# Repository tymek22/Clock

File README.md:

# Clock

<br>This smart Clock is made to resemble a traditional wall clock. It shows the time using two rings of RGB LEDs. The inner (smaller) ring is for the hours, while the outer circumference displays the minutes together with the seconds.
<br>The clock is a smart clock, it features a microcontroller which has BLE connectivity. By using a mobile application, the clock can be controlled wirelessly. Below is a photo of the clock showing the time 9:41

## <b>Components</b><br>
The clock is built from various components and materials. The main ones are:
 - Frame, 3D printed
 - Power supply, 5V adapter with sufficient power
 - RGB LED strips, 1 strip of 60 and 1 strip of 48 LEDs (WS2812b)
 - PIR sensor
 - CR2032 battery
 - Wires
 - PCB
 - Other components for the PCB
 
## <b>Frame</b><br>
 
 The frame has been designed in Autodesk Fusion 360. It looks like this:<br>
 <br>
 
 The electronics are placed inside, the only components which are outside of the clock body are the LEDs as well as the wires to a power adapter. Below on the left, you can see the inside of the body and on the right, how it looks in reality.<br>

<p>&nbsp;</p>
Because of all those wires, it looks very messy, but fortunately, this can not be seen from the outside.
The fact that one meter of such a LED strip contains 60 LEDs makes it easy, because one hour has 60 minutes. So each LED represents a minute or second. The inner circle is smaller, so 60 LEDs can't fit there.
I have chosen the number of LEDs for the hours to be 48, firstly, because it's a multiple of 12 (and there are 12 hours on a clock). And secondly, that makes the inner circle's circumference 80cm, which fits physically well. Below, the alignment
of the LEDs on the clock casing is shown. The first LED does not start at the top and to make things more complicated, the LEDs run counter-clockwise. Of course it would be better to have the LEDs arranged more logically,
but it was not possible to easily mount it in that way. It's not a big problem, because the arrangement of LEDs can be addressed in software.
 <br>
 <p>&nbsp;</p>
 
## <b>Connections</b><br>

<br>
Here is an overview of the connections. These are all the components, which are not directly on the PCB, but are inside the case. These parts can not be put directly on the PCB, because they are mounted too far away from each other.

## <b>Schematic and PCB</b><br>

<p>&nbsp;</p> 
Here you can see the schematic and the PCB layout. The brain of the clock is a Cypress CYBLE-224110-00. It is a module which includes everything what is needed. There are many other Bluetooth modules,
like the NRF51822 or ESP32. However, I have chosen this module over the alternatives, because of its clear IDE and good documentation. It is also very flexible regarding the pins and peripherals.
It features runtime reconfigurable serial communication blocks, as well as programmable logic blocks.
The Cypress module is an ARM Cortex M0 microcontroller, with Bluetooth Low Energy (BLE) and all standard peripherals. This module runs at 3.3V, but the power supply is 5V, so obviously, some voltage regulator is needed.
This is handled by the TLV733P, a simple 5V to 3.3V low-dropout regulator. I liked it because it's small and doesn't require a capacitor to function properly. Because of this, its total footprint is very minimal.
There are two more ICs used. One of them is the DS3231, a famous real-time clock. It's precise and doesn't need an external crystal oscillator. Additionally, it can output a 1Hz square wave at a pin, which makes it ideal for a clock application.
The last major component is SN74AHCT125, a quadruple bus buffer gate, which in my case is used as a voltage level shifter. It converts the 3.3V output of the microcontroller to 5V, which goes to the LED strips.
I tried to make the PCB as small as possible, so it could fit easily inside the case, but also to save on costs. Around the edges, there are multiple pins for various reasons. Some are to connect the MCU with other components,
and some are used for debugging only. 

## <b>Power Consumption</b><br>
All values were measured at maximum brightness.

|  Configuration | Current Draw | Voltage | Power |
| ------------- | ------------- | --- | --- |
| No LEDs  | 78 mA  |  5.39 V |  0.42 W |
| Lamp with one color  | 1.58 A  |  5.25 V |  8.30 W |
| Lamp with white color | 4.17 A |  5.02 V |  20.93 W |
| Low-power clock |  120 mA |  5.38 V |  0.65 W |
| High-power clock |  850 mA |  5.30 V |  4.51 W |

## <b>Software</b><br>
#### MCU Firmware<br>
The firmware is created in the PSoC Creator IDE from Cypress. It runs on the CYBLE-224110-00 module. The module can be upgraded wirelessly by a BLE OTA update.
The main files and code reside in the `CYBLE-224110-00 Clock firmware.cydsn` folder and the code itself is explained using comments.<br>
The RTC is communicating with the MCU via I2C and the RTC outputs a 1Hz square wave. This square wave is used as an interrupt, to easily let the microcontroller check the time every second and update the LEDs.<br>
There is also a PIR sensor. The purpose of this sensor is to check whether there is a person nearby. If there is no one, the clock can show the time with less LEDs turned on, to save on electricity. The full array of LEDs is only used when
there is actually someone who can see it.<br>
Additionally, an LDR is used to see how light or dark it is. This information is used to automatically set the brightness of the clock. If it's really dark (at night), the clock displays the time in the power-saving mode too, so it's not emitting
too much light at night.

#### iOS App<br>
The mobile app is developed for iOS only, as at the time of development my main mobile phone was an iPhone. It is created in XCode, Apple's IDE. The app can fully control the clock. It can set the time to either the iPhone's time,
or to a custom value input by the user. The clock can also be put in the Device Firmware Update (DFU) mode, in which the clock can receive an OTA update. The clock has a feature where it can become a lamp and this
can also be controlled from the application. The user can choose a color and a brightness and send it to the clock. This lamp mode can obviously be turned off as well. Lastly, the app displays some information from the clock.
It shows whether the clock is in the lamp mode. Whether the PIR is on or off. And the light intensity is shown as well. It's also possible to see the temperature of the clock, but this is of limited use, because the temperature inside the
case differs from the outside temperature. I included the temperature for debugging and safety purposes only.

## <b>Improvements</b><br>
In retrospect, I see that there are points to improve on.
<br>One of them is the clock frame. For a next version, I would make proper mounting for all parts, so they don't just sit inside the case, but are firmly attached somewhere. A fixed position would also make the wiring easier,
but because I started from scratch without any reference, it was difficult to set fixed positions for everything, I needed this little flexibility.
<br>Initially, I wanted to use a connector for the power input to the clock, but the connector turned out to be too big. I didn't use the connector and just soldered the cable directly inside the casing. It would be better to have a connector,
so the next time, I would look for a nice one and add it.
<br>Another thing is the PCB. I used only the first revision in the final product, so all errors had to be fixed manually. However, if I was to make a new revision, I would change a few things. The main issue was with the breakout pins.
I would change all pins to one sort. It would be nice if the LDR had its own pins as well, instead of the small SMD pads. In reality, the pads were smaller than I thought and it was hard to solder the leads. It worked for some time,
but after a while, the wires broke and one pad came off. I solved this by reusing the UART Tx pin for the LDR. The Tx pin was not needed anyway, because this issue appeared at the later stages of debugging and I used Bluetooth to see
all data.
<br>As for the software, it would be nice to do something with the LED colors. Some kind of animations and/or random color variations. The iOS app could get a better UI as well. I know that I'm not a good designer, so now it's
just functional and not very nice.

<p>&nbsp;</p>

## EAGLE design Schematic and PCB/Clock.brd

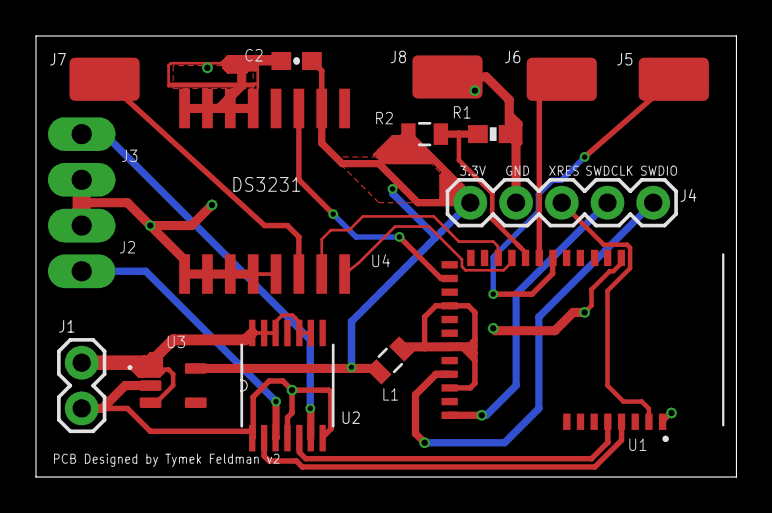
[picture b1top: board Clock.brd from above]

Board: 2 copper layers, 38.9 x 24.5 mm, 16 parts (0 on the bottom side), 18 nets.

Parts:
C2: 100nF; 0603-CAP
J1: 5V In; 1X02
J2: LedStripHour; 1X02_LONGPADS
J3: LedStripMinute; 1X02_LONGPADS
J4: 1X05
J5: PIR; LUXEON-PAD
J6: TX; LUXEON-PAD
J7: Vbat; LUXEON-PAD
J8: GND; LUXEON-PAD
L1: 330Ω 100MHz; 0805
R1: 10k; 0603-RES
R2: LDR; 0805
U1: CYBLE-224110-00; CYPRESS_CYBLE-224110-00
U2: SN74AHCT125PW; SOP65P640X120-14N
U3: TLV73333PDBVT; SOT95P280X145-5N
U$1: DS3231; SO16W

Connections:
3.3V: C2.1, J4.5, L1.2, R2.2, U3.5, U$1.2
5V: J1.2, U2.9, U2.10, U2.12, U2.13, U2.14, U3.1, U3.3
GND: C2.2, J1.1, J2.1, J3.1, J4.4, J8.P$1, R1.1, U1.1, U1.32, U2.1, U2.4, U2.7, U3.2, U$1.5, U$1.6, U$1.7, U$1.8, U$1.9, U$1.10, U$1.11, U$1.12, U$1.13
HOUR: U1.4, U2.2
HOURTRACE: J2.2, U2.3
LDR: R1.2, R2.1, U1.25
MINUTE: U1.5, U2.5
MINUTETRACE: J3.2, U2.6
unnamed: J7.P$1, U$1.14
unnamed: L1.1, U1.11, U1.14, U1.17
PIR: J5.P$1, U1.27
SCL: U1.24, U$1.16
SDA: U1.23, U$1.15
SQW: U1.19, U$1.3
SWDCLK: J4.2, U1.9
SWDIO: J4.1, U1.12
TX: J6.P$1, U1.26
XRES: J4.3, U1.2

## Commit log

2019-12-29 Add .gitignore and update files accordingly
2019-12-29 Remove unneeded files
2019-12-29 Fix project dependency and update .gitignore
2019-12-29 Fix dependency
2019-12-29 Change types of variables
2019-12-29 Add generation of random hands colors at startup and improve code readability
2020-01-01 Remove unneeded Xcode project files

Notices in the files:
Schematic and PCB/Clock.brd:
Copyright © 2019
parts and their libraries:
SparkFun-Capacitors: Licensing: Creative Commons ShareAlike 4.0 International - https://creativecommons.org/licenses/by-sa/4.0
